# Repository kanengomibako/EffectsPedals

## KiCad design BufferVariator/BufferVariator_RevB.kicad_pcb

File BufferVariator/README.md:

# Buffer Variator
<br>

ギター・ベースのピックアップで拾った音は、楽器本体のボリューム・トーンやシールドケーブル、最初に接続する機器の入力部により独特な音質変化が起こります。本機は、入力部の抵抗値と静電容量値を変化させることにより、主に高音域の音質変化をコントロールできるようにしたバッファー／ブースターです。

### 各部の機能

- INPUT 端子

  パッシブタイプのギターやベースを接続します。フルアップボリュームポットやフルアップトーンポットが搭載されていると、より効果的です。アクティブタイプの楽器や別のバッファーを介して接続した場合、音色変化がほとんどなく、GAINのみ変化します。

- OUTPUT 端子

  アンプや他の機器の入力へ接続します。

- DC9V 端子

  ACアダプターなどの電源を接続します。電源には、DC9V（センターマイナス）出力で、100mA以上の電流出力が可能なものを使用してください。

  ※ 12V以上の電源を接続した場合は、保護回路が働くため動作しません。

- フットスイッチ

  エフェクトオン／オフを切り替えます。エフェクトオフ時は、一般的なバッファー（RESISTANCE：1MΩ　CAPACITANCE：OFF　GAIN：±0dB）となります。

  ※ 一般的なトゥルーバイパスのエフェクターと同程度のスイッチングノイズがあります。

- GAIN

  音量の増減を調整します。

- RESISTANCE

  抵抗値を設定します。抵抗値が上がるほど、高音域が強調された音色になります。代表的な周波数特性変化は下図の通りです。

  <br>※ 10kから反時計回り、10Mから時計回りにはストッパーがあるため回りません。無理な力を加えないようご注意ください。

- CAPACITANCE

  コンデンサの静電容量を設定します。容量値が上がるほど、高音域が減衰した音色になります。ピックアップの種類によりますが、ピークレベルも少し変動します。代表的な周波数特性変化は下図の通りです。

  <br>※ OFFから反時計回り、6800pから時計回りにはストッパーがあるため回りません。無理な力を加えないようご注意ください。

### 使い方の例

- バッファー／ブースター／アッテネーター

  通常のイコライザーでは再現が難しい音色変化があります。音量を上げるだけでなく、下げる目的でも使用することができます。

- シールドケーブルシミュレーション

  シールドケーブルにはコンデンサのように静電容量があります。ケーブルの長さに比例して容量値が大きくなるので、短いケーブルを使用しているときに本機で容量を足すと、長いケーブルを使っているときと同じ音色にすることができます。また、使用したいケーブルの静電容量がわかっている場合、それと同じ容量になるように設定することができます。

- エフェクター入力部の再現

  一部のエフェクターでは、前段にバッファーがあると音色が変化します。そういったエフェクターの前段に使うバッファーとして本機を以下のような設定にしておくと、バッファーなしで接続したときの音をある程度再現することができます。
  
  | 機種             | RESISTANCE | CAPACITANCE |
  | ---------------- | ---------- | ----------- |
  | RAT、Distortion+ | 1M         | 1000p       |
  | Big Muff         | 50k        | OFF         |
  | Fuzz Face        | 10k        | OFF         |
  
  ※ Fuzz Faceは再現度が高くありません。

### 資料
- [Buffer Variator製作に関する記事](https://kanengomibako.github.io/pages/00386_BufferVariator.html)
- [「ボリューム」で考える入出力インピーダンス](https://kanengomibako.github.io/pages/00301.html)
- [ギターケーブルの音への影響](https://zenn.dev/bj_9/articles/ef8c6669f2db6e)（外部サイト）

| 主な仕様 |  |
| - | - |
| 最大入力電圧 | +15.9 dBu（13.7 Vp-p） |
| 最大出力電圧 | +15.7 dBu（13.4 Vp-p） |
| 入力インピーダンス | 1 MΩ（エフェクトオフ時） |
| 出力インピーダンス | 1 kΩ |
| コントロール | エフェクトオン／オフスイッチ　RESISTANCEつまみ　CAPACITANCEつまみ　GAINつまみ |
| インジケーター | 青色LED（エフェクトオン）<br>暗赤色LED（エフェクトオフ） |
| 接続端子 | INPUT端子　OUTPUT端子　電源入力端子 |
| 消費電流 | 16 mA |
| 外形寸法 | 幅 63 mm × 奥行 110 mm × 高さ 51 mm<br/>（つまみ、スイッチ部を除いた高さ 34 mm） |
| 質量 | 306 g（ステンレス筐体バージョン）<br>196 g（アルミニウム筐体バージョン） |

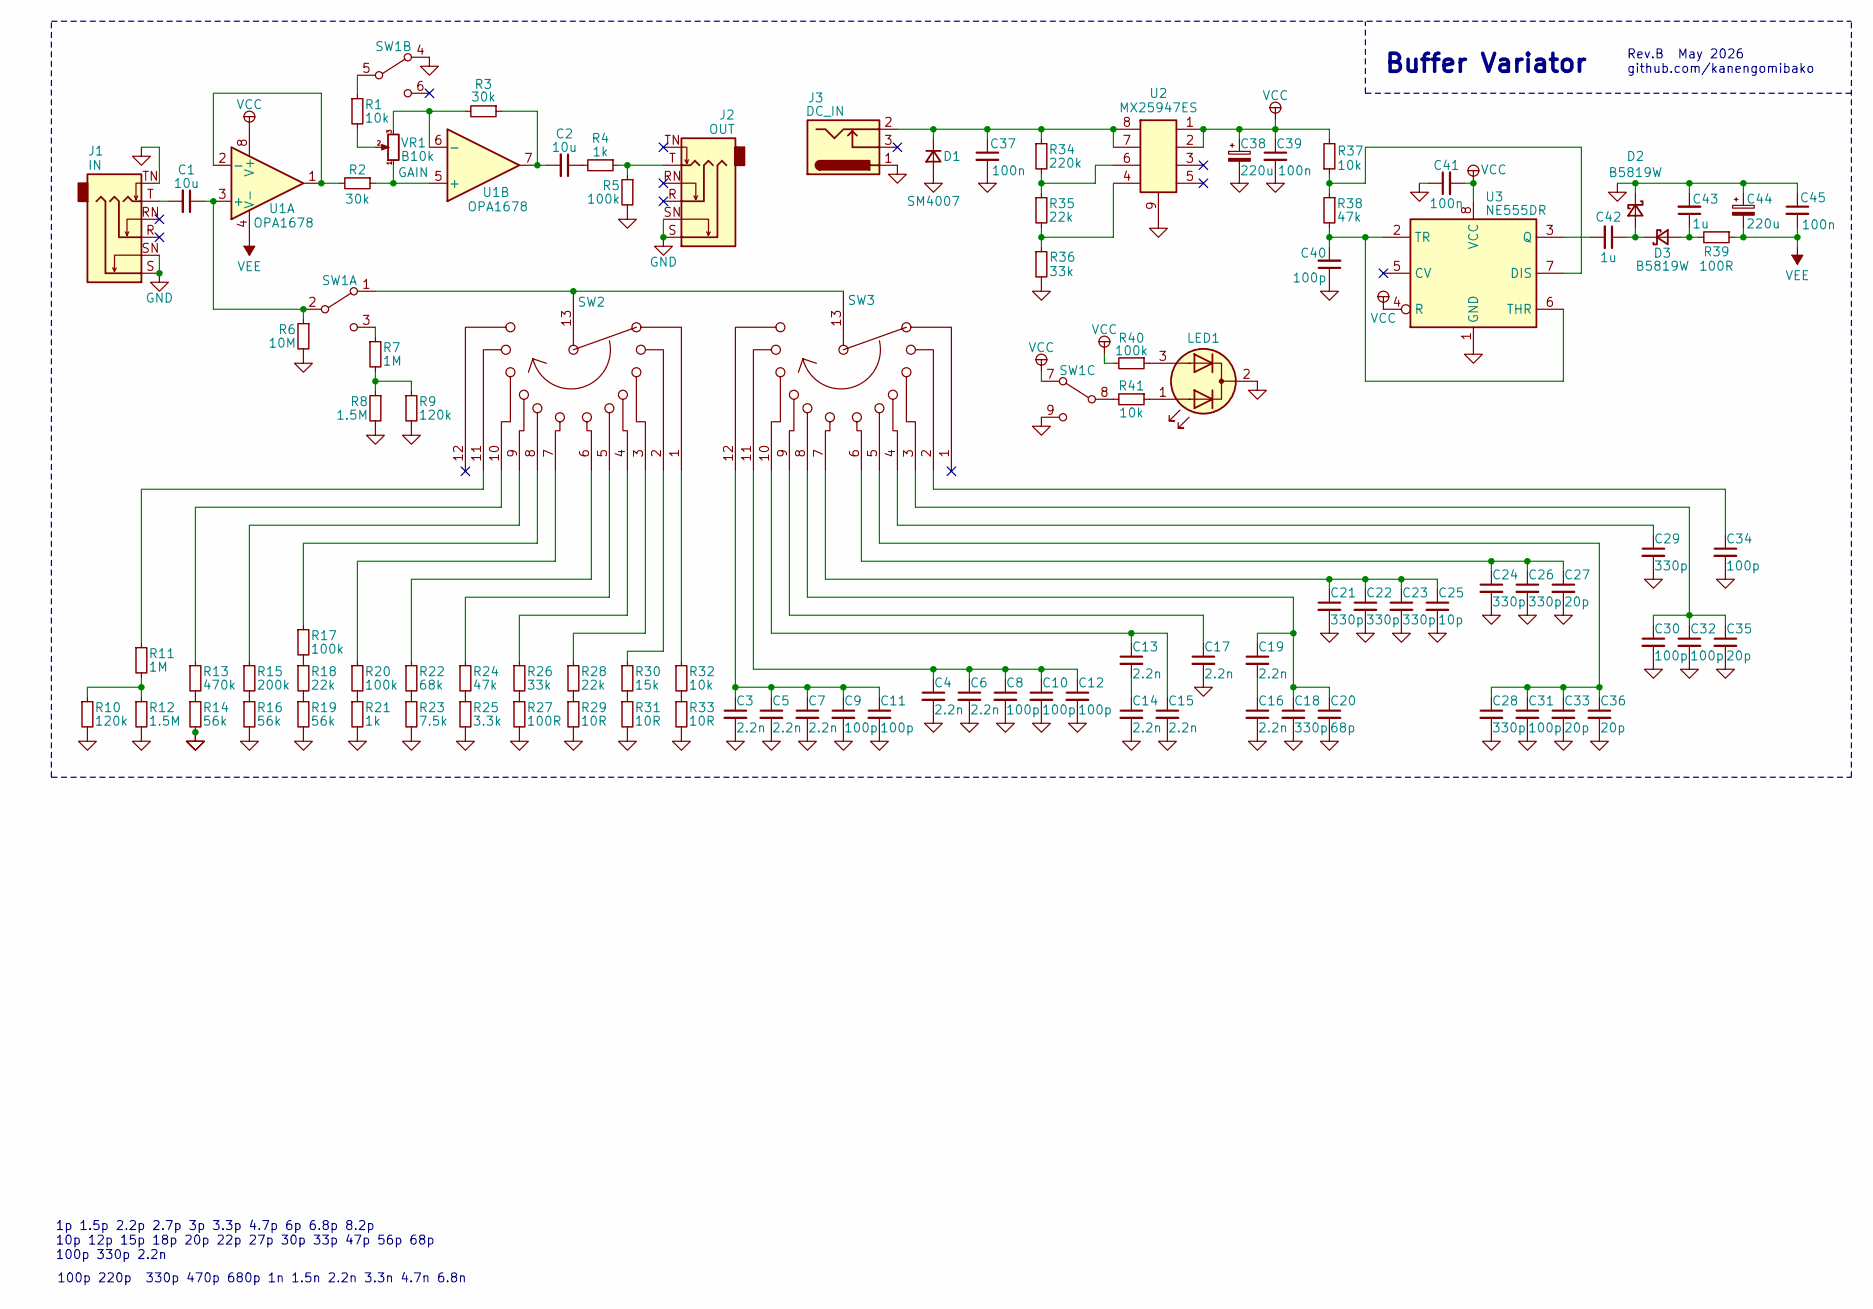
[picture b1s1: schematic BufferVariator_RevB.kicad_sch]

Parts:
C1, C2: 10u; C_1812_4532Metric_THT_P2.0; LCSC C399604
C3, C4, C5, C6, C7, C13, C14, C15, C16, C17, C19: 2.2n; C_0805_2012Metric; LCSC C28260
C8, C9, C10, C11, C12, C30, C31, C32, C34, C40: 100p; C_0603_1608Metric; LCSC C14858
C18, C21, C22, C23, C24, C26, C28, C29: 330p; C_0603_1608Metric; LCSC C1664
C20: 68p; C_0603_1608Metric; LCSC C28262
C25: 10p; C_0603_1608Metric; LCSC C1634
C27, C33, C35, C36: 20p; C_0603_1608Metric; LCSC C1648
C37, C39, C41, C45: 100n; C_0603_1608Metric; LCSC C14663
C38, C44: 220u; my_C_D6.3mm_P2.50mm; LCSC C88729
C42, C43: 1u; C_1206_3216Metric; LCSC C1848
D1: SM4007; D_SOD-123F; LCSC C64898
D2, D3: B5819W; D_SOD-123F; LCSC C8598
J1: IN; PJ-611E_HOOYA; LCSC C309282
J2: OUT; PJ-611E_HOOYA; LCSC C309282
J3: DC_IN; my_DC_Jack; LCSC C319099
LED1: BR_LED; my_LED_3mm_RG; LCSC C2895559
R1, R32, R37, R41: 10k; R_0603_1608Metric; LCSC C25804
R2, R3: 30k; R_0603_1608Metric; LCSC C22984
R4, R21: 1k; R_0603_1608Metric; LCSC C21190
R5, R17, R20, R40: 100k; R_0603_1608Metric; LCSC C25803
R6: 10M; R_0603_1608Metric; LCSC C7250
R7, R11: 1M; R_0603_1608Metric; LCSC C22935
R8, R12: 1.5M; R_0603_1608Metric; LCSC C4172
R9, R10: 120k; R_0603_1608Metric; LCSC C25808
R13: 470k; R_0603_1608Metric; LCSC C23178
R14, R16, R19: 56k; R_0603_1608Metric; LCSC C23206
R15: 200k; R_0603_1608Metric; LCSC C25811
R18, R28, R35: 22k; R_0603_1608Metric; LCSC C31850
R22: 68k; R_0603_1608Metric; LCSC C23231
R23: 7.5k; R_0603_1608Metric; LCSC C23234
R24, R38: 47k; R_0603_1608Metric; LCSC C25819
R25: 3.3k; R_0603_1608Metric; LCSC C22978
R26, R36: 33k; R_0603_1608Metric; LCSC C4216
R27, R39: 100R; R_0603_1608Metric; LCSC C22775
R29, R31, R33: 10R; R_0603_1608Metric; LCSC C22859
R30: 15k; R_0603_1608Metric; LCSC C22809
R34: 220k; R_0603_1608Metric; LCSC C22961
SW1: 3PDT; my_sw_3pdt; LCSC Daier
SW2: Rotary_SW_R; RotarySW_Alpha_26mm_wide_pad; LCSC A-1893 Tayda
SW3: Rotary_SW_C; RotarySW_Alpha_26mm_wide_pad; LCSC A-1893 Tayda
U1: OPA1678; SOIC-8_3.9x4.9mm_P1.27mm_rotate; LCSC C192421
U2: MX25947ES; SOIC-8-1EP_3.9x4.9mm_rotate; LCSC C5875698
U3: NE555DR; SOIC-8_3.9x4.9mm_P1.27mm_rotate; LCSC C7593
VR1: B10k; my_Pot_RD901F-40; LCSC A-7788 Tayda

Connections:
GND: C3.2, C4.2, C5.2, C6.2, C7.2, C8.2, C9.2, C10.2, C11.2, C12.2, C14.2, C15.2, C16.2, C17.2, C18.2, C20.2, C21.2, C22.2, C23.2, C24.2, C25.2, C26.2, C27.2, C28.2, C29.2, C30.2, C31.2, C32.2, C33.2, C34.2, C35.2, C36.2, C37.2, C38.2, C39.2, C40.1, C41.1, C43.2, C44.1, C45.1, D1.2 (A), D2.1 (K), J1.S, J1.SN, J1.TN, J2.S, J2.SN, J3.1, LED1.2 (K), R5.2, R6.2, R8.2, R9.2, R10.2, R12.2, R14.2, R16.2, R19.2, R21.2, R23.2, R25.2, R27.2, R29.2, R31.2, R33.2, R36.2, SW1.4 (A), SW1.9 (C), U2.9 (Pin_8), U3.1 (GND)
unnamed: C1.2, J1.T
unnamed: C2.1, R4.2
unnamed: C2.2, R3.1, U1.7
unnamed: C4.1, C6.1, C8.1, C10.1, C12.1, SW3.11
unnamed: C3.1, C5.1, C7.1, C9.1, C11.1, SW3.12
unnamed: C13.1, C15.1, SW3.10
unnamed: C13.2, C14.1
unnamed: C16.1, C19.2
unnamed: C17.1, SW3.9
unnamed: C18.1, C19.1, C20.1, SW3.8
unnamed: C21.1, C22.1, C23.1, C25.1, SW3.7
unnamed: C24.1, C26.1, C27.1, SW3.6
unnamed: C28.1, C31.1, C33.1, C36.1, SW3.5
unnamed: C29.1, SW3.4
unnamed: C30.1, C32.1, C35.1, SW3.3
unnamed: C34.1, SW3.2
unnamed: C37.1, D1.1 (K), J3.2, R34.1, U2.7, U2.8
unnamed: C42.1, D2.2 (A), D3.1 (K)
unnamed: C43.1, D3.2 (A), R39.2
unnamed: J2.T, R4.1, R5.1
unnamed: LED1.1 (A1), R41.1
unnamed: LED1.3 (A2), R40.1
unnamed: R1.2, VR1.2
unnamed: R7.2, R8.1, R9.1
unnamed: R10.1, R11.2, R12.1
unnamed: R11.1, SW2.11
unnamed: R13.1, SW2.10
unnamed: R13.2, R14.1
unnamed: R15.1, SW2.9
unnamed: R15.2, R16.1
unnamed: R17.1, SW2.8
unnamed: R17.2, R18.1
unnamed: R18.2, R19.1
unnamed: R20.1, SW2.7
unnamed: R20.2, R21.1
unnamed: R22.1, SW2.6
unnamed: R22.2, R23.1
unnamed: R24.1, SW2.5
unnamed: R24.2, R25.1
unnamed: R26.1, SW2.4
unnamed: R26.2, R27.1
unnamed: R28.1, SW2.3
unnamed: R28.2, R29.1
unnamed: R30.1, SW2.2
unnamed: R30.2, R31.1
unnamed: R32.1, SW2.1
unnamed: R32.2, R33.1
unnamed: SW1.1 (A), SW2.13, SW3.13
unnamed: C1.1, R6.1, SW1.2 (B), U1.3 (+)
unnamed: R7.1, SW1.3 (C)
unnamed: R1.1, SW1.5 (B)
unnamed: R41.2, SW1.8 (B)
unnamed: R2.2, U1.1, U1.2 (-)
unnamed: R2.1, U1.5 (+), VR1.1
unnamed: R3.2, U1.6 (-), VR1.3
unnamed: R35.2, R36.1, U2.4
unnamed: R34.2, R35.1, U2.6
unnamed: R37.1, R38.1, U3.7 (DIS)
unnamed: C42.2, U3.3 (Q)
unnamed: C40.2, R38.2, U3.2 (TR), U3.6 (THR)
VCC: C38.1, C39.1, C41.2, R37.2, R40.2, SW1.7 (A), U1.8 (V+), U2.1, U2.2, U3.4 (R), U3.8 (VCC)
VEE: C44.2, C45.2, R39.1, U1.4 (V-)

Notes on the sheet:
100p 220p 330p 470p 680p 1n 1.5n 2.2n 3.3n 4.7n 6.8n
Buffer Variator
1p 1.5p 2.2p 2.7p 3p 3.3p 4.7p 6p 6.8p 8.2p 10p 12p 15p 18p 20p 22p 27p 30p 33p 47p 56p 68p 100p 330p 2.2n
Rev.B May 2026 github.com/kanengomibako

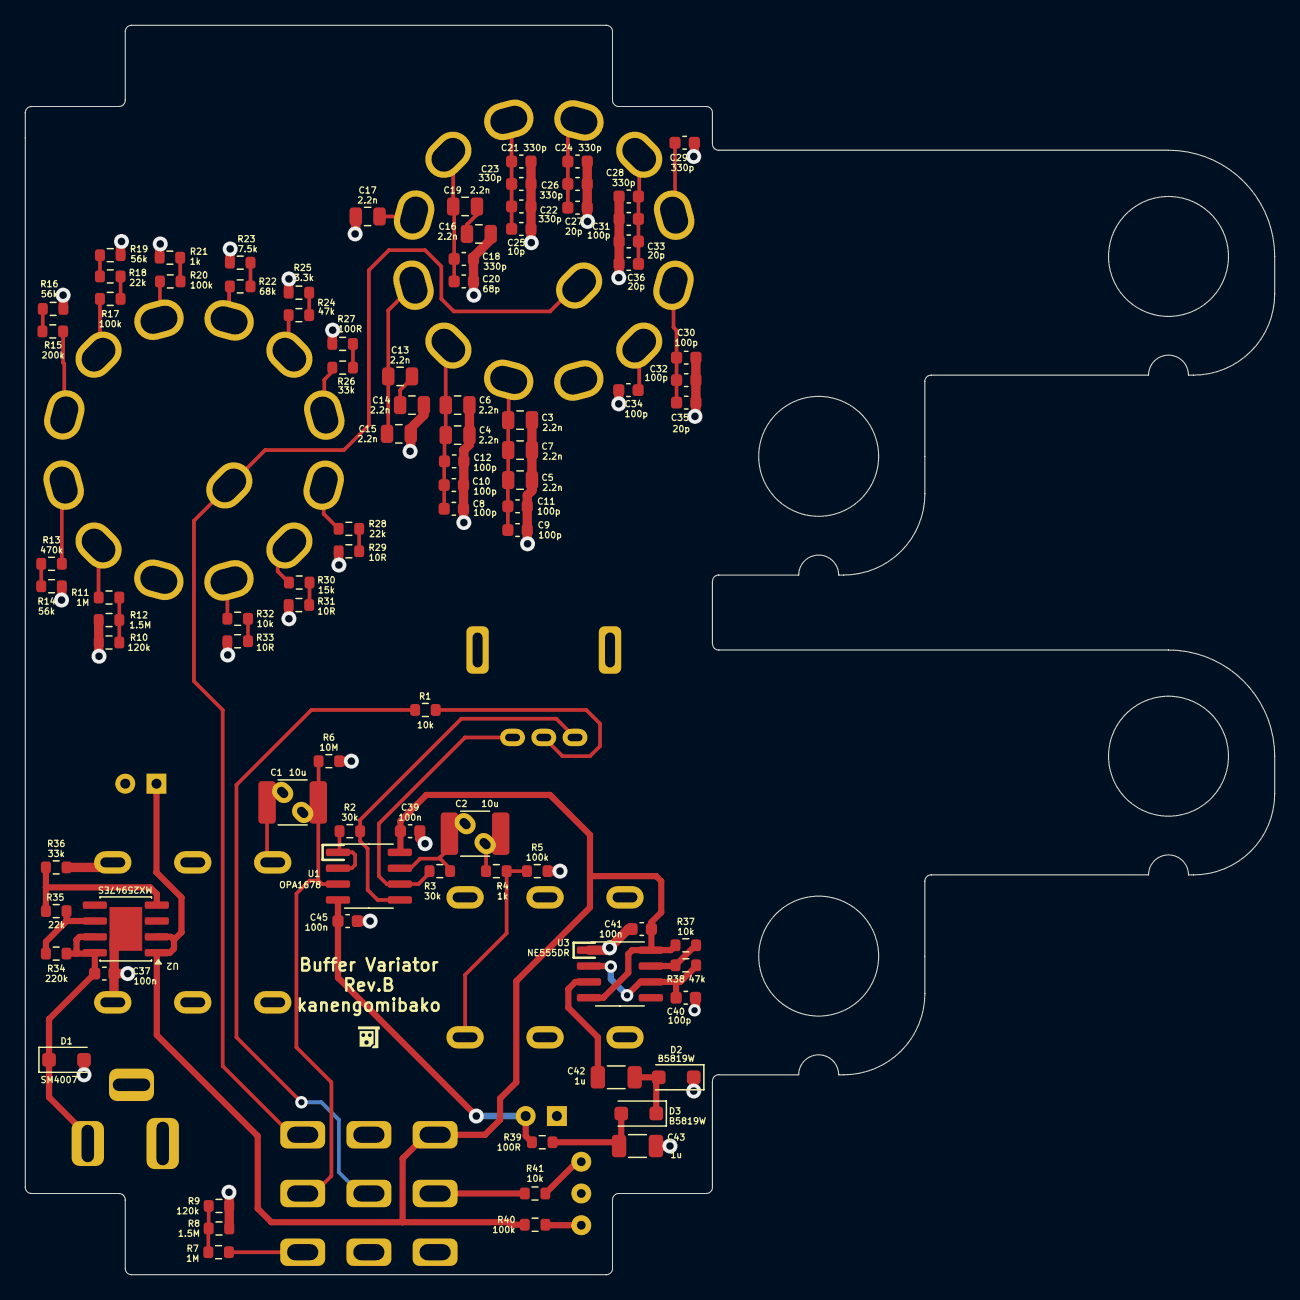
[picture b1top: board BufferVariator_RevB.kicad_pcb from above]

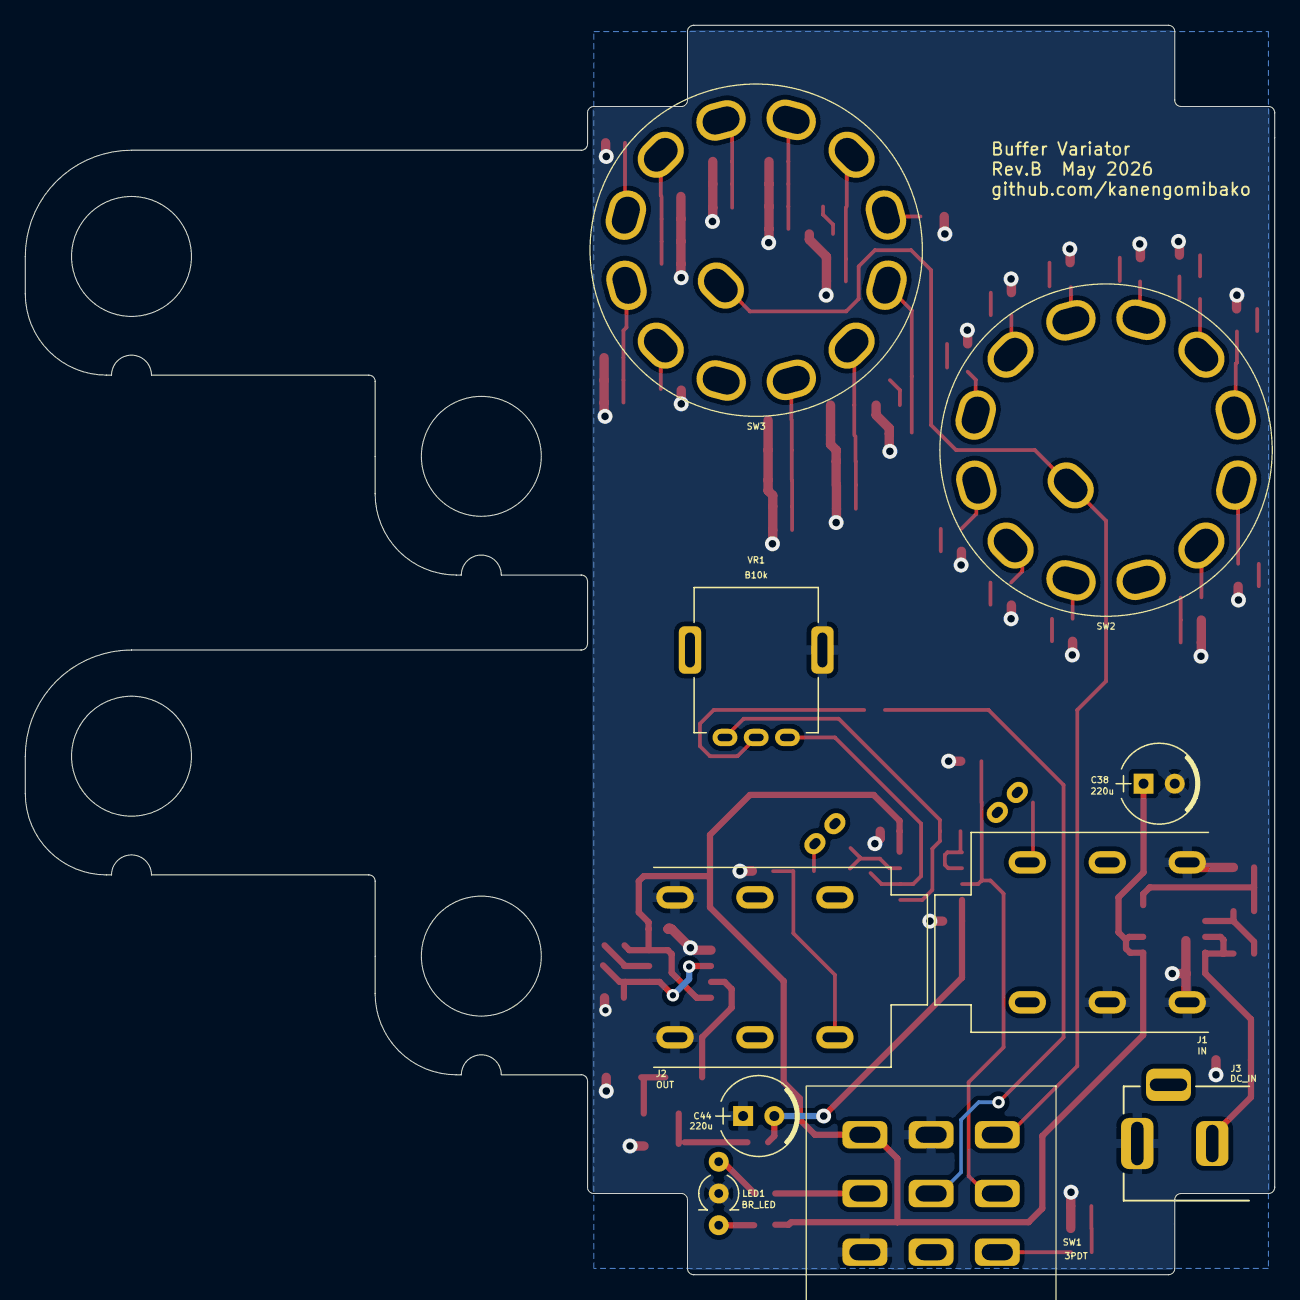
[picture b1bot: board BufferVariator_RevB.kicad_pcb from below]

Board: 2 copper layers, 100.0 x 100.0 mm, 100 parts (10 on the bottom side), 63 nets.

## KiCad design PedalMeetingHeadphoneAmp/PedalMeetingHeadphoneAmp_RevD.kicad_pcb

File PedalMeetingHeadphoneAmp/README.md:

# Pedal Meeting Headphone Amp
<br>

エフェクター展示会の試奏ブースでのコミュニケーションを円滑にするために設計されたヘッドフォンアンプです。ギター／ベースの音と会話用のマイク音声をミックスし、ヘッドフォンで聴くことができます。試奏者と出展者が音を共有できると共に、ヘッドフォンを外さずに会話することが可能となります。

※ 電源は、DC9V（センターマイナス）出力のACアダプターで、0.3A以上の電流出力が可能なものを使用してください。

### ■ 入力

それぞれ独立したゲイン調整を備えています。ゲインを上げ過ぎるとハウリングが起こることがありますのでご注意ください。

- INST

  楽器側の音声出力を接続します。アンプ・キャビネットシミュレータからの接続を想定しています。ゲインは基本的に中央で固定し、微調整として使用してください。

- MIC1／MIC2

  外部マイクを接続します。48Vファンタム電源が必要なマイクには対応していません。

- MIC3

  本体トップ面にあるマイクです。外部マイクがない場合でも、会話を拾うことが可能です。

### ■ 出力

楽器の音とマイクの音をそれぞれ出力ボリュームで調整できます。

- PHONES A／B

  試奏者用、出展者用のヘッドフォンを接続します。

- LINE A／B

  外部録音機器を接続できます。

### ■ スイッチ

- MIC ON／OFF

  すべてのマイク入力を一括でミュートします。マイクが楽器の生音を拾うため、会話時以外はマイクをOFF（LED消灯）にすることをお勧めします。

- MIC 5V

  プラグインパワー方式のコンデンサーマイク（[BEHRINGER BC LAV](https://www.electori-br.jp/products/1043.html) 等）を使用する際にONにします。ダイナミックマイク接続時はOFFにします。48Vファンタム電源が必要なマイクには対応していません。

### ■ 資料
- [Pedal Meeting Headphone Amp製作に関する記事](https://kanengomibako.github.io/pages/00384_PedalMeetingHeadphoneAmp.html)

- ブロック図

  <br>

| ■ 主な仕様 |  |
| - | - |
| 入力インピーダンス | 47kΩ（INST）<br>10kΩ（MIC） |
| 出力インピーダンス | 1 kΩ（LINE）<br>10Ω（PHONES） |
| 最大出力レベル | 2.5 Vrms（LINE）<br>50 mW + 50 mW, 32Ω（PHONES） |
| コントロール | MIC ON／OFFスイッチ　MIC 5Vスイッチ　GAINつまみ × 4　VOLつまみ × 4 |
| インジケーター | 赤色LED（電源ON）<br>青色LED（マイクON） |
| 接続端子 | INST　MIC1／2　PHONES A／B　LINE A／B　電源入力端子 |
| 消費電流 | 40 mA（無信号時）<br>300 mA（最大出力時） |
| 外形寸法 | 幅 100 mm × 奥行 130 mm × 高さ 57 mm |
| 質量 | 550 g |

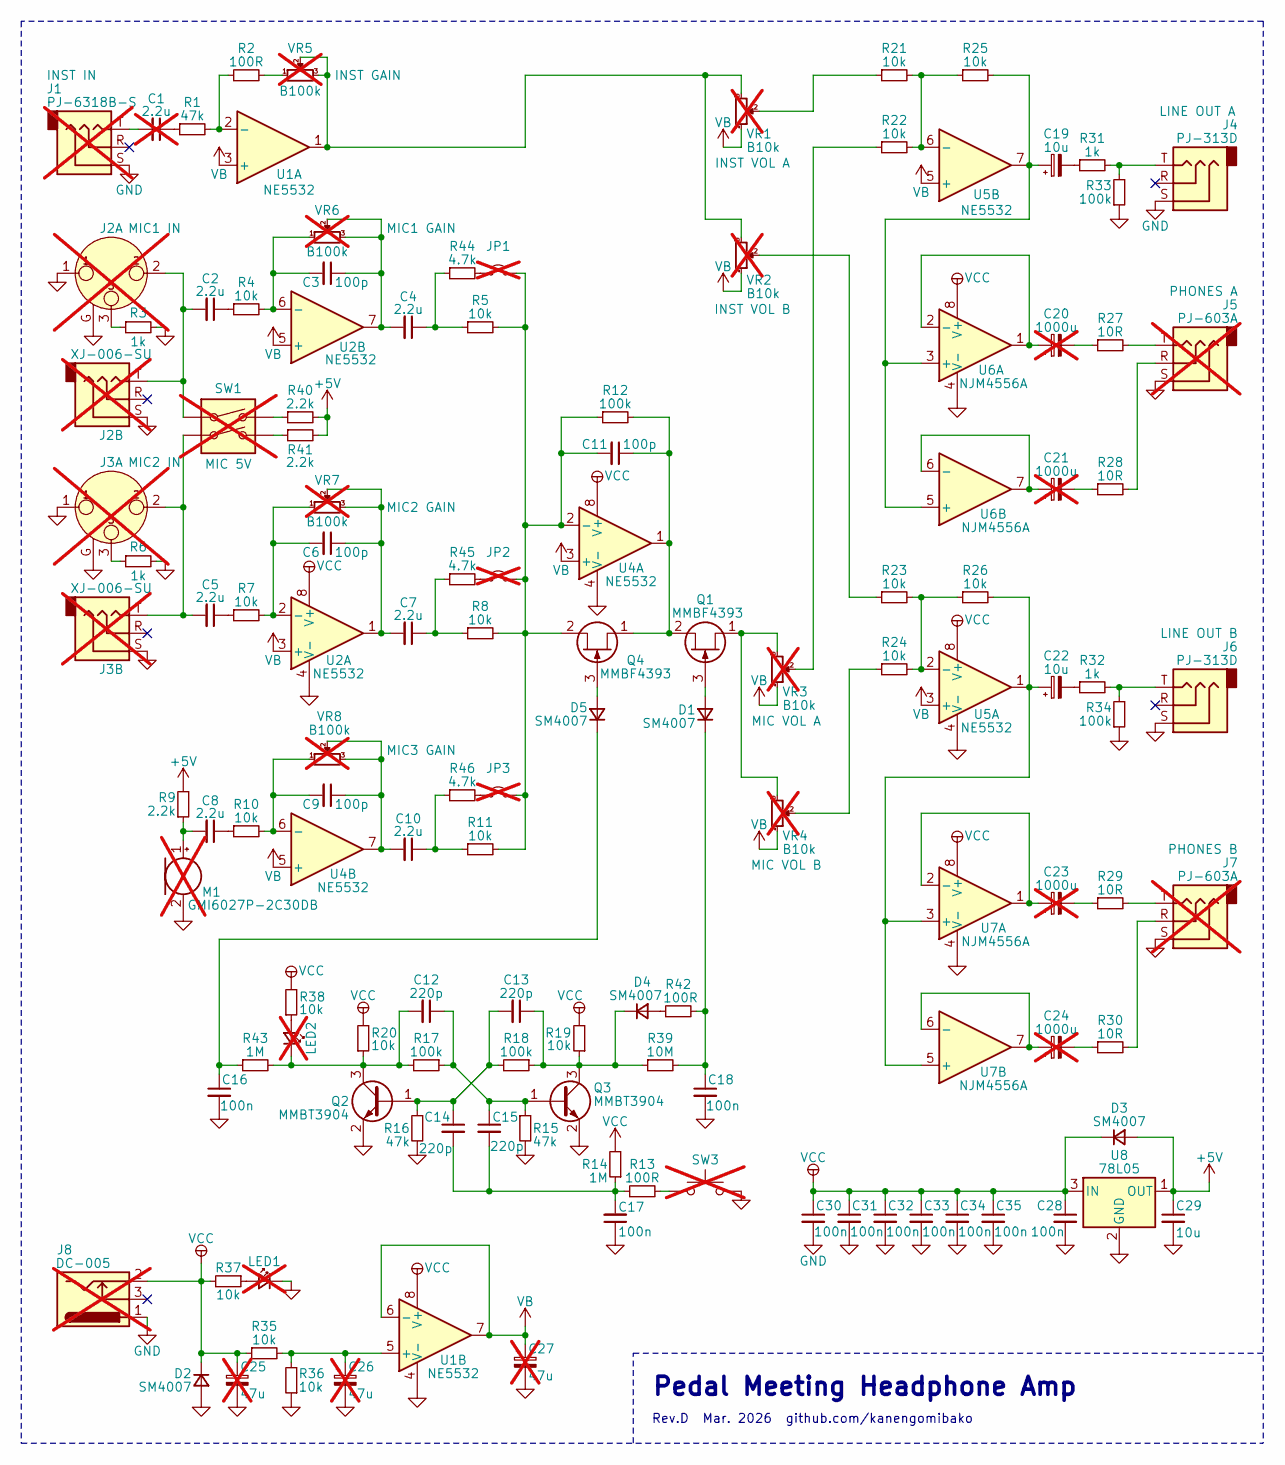
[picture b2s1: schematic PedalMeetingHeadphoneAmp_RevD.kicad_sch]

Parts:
C1: 2.2u; CP_3216-THD; LCSC C178482; not fitted
C2, C4, C5, C7, C8, C10: 2.2u; C_0805_2012Metric; LCSC C377773
C3, C6, C9, C11: 100p; C_0603_1608Metric; LCSC C14858
C12, C13, C14, C15: 220p; C_0603_1608Metric; LCSC C1603
C16, C17, C18, C28, C30, C31, C32, C33, C34, C35: 100n; C_0603_1608Metric; LCSC C14663
C19, C22: 10u; CP_3216-THD; LCSC C7171
C20, C21, C23, C24: 1000u; CP_Radial_D10.0mm_P5.00mm; LCSC C338175; not fitted
C25, C26, C27: 47u; CP_Radial_D5.0mm_P2.00mm; LCSC C216203; not fitted
C29: 10u; C_0805_2012Metric; LCSC C15850
D1, D2, D3, D4, D5: SM4007; D_SOD-123F; LCSC C64898
J1: PJ-6318B-S; PJ-6318; LCSC C50176625; not fitted
J2, J3: XJ-006-SU; Jack_XLR-6.35mm_Neutrik_NCJ6FA-H-0_Horizontal; LCSC C309332; not fitted
J4, J6: PJ-313D; PJ-313D_HOOYA; LCSC C2939579
J5, J7: PJ-603A; LCSC C309273; not fitted
J8: DC-005; my_DC_Jack; LCSC C319099; not fitted
JP1, JP2, JP3: JP; my_SolderJumper-THpad; not fitted
LED1: Red_LED; my_LED_3mm; LCSC C440523; not fitted
LED2: Blue_LED; my_LED_3mm; LCSC C330760; not fitted
M1: GMI6027P-2C30DB; my_conn; LCSC C233898; not fitted
Q1, Q4: MMBF4393; SOT-23_rotate; LCSC C152291
Q2, Q3: MMBT3904; SOT-23_rotate; LCSC C20526
R1, R15, R16: 47k; R_0603_1608Metric; LCSC C25819
R2, R13, R42: 100R; R_0603_1608Metric; LCSC C22775
R3, R6, R31, R32: 1k; R_0603_1608Metric; LCSC C21190
R4, R5, R7, R8, R10, R11, R19, R20, R21, R22, R23, R24, R25, R26, R35, R36, R37, R38: 10k; R_0603_1608Metric; LCSC C25804
R9, R40, R41: 2.2k; R_0603_1608Metric; LCSC C4190
R12: 100k; my_R_0603_smd_thd_P7mm; LCSC C25803
R14, R43: 1M; R_0603_1608Metric; LCSC C22935
R17, R18, R33, R34: 100k; R_0603_1608Metric; LCSC C25803
R27, R28, R29, R30: 10R; R_1206_3216Metric; LCSC C17903
R39: 10M; R_0603_1608Metric; LCSC C7250
R44, R45, R46: 4.7k; R_0603_1608Metric; LCSC C23162
SW1: SW_DIP; SW_DIP_SPSTx02_Slide_9.78x7.26mm_W7.62mm_P2.54mm; LCSC C3040968; not fitted
SW3: SW; SW_Cherry_MX_1.00u_PCB; LCSC C412378; not fitted
U1, U2, U4, U5: NE5532; SOIC-8_3.9x4.9mm_P1.27mm_rotate; LCSC C7426
U6, U7: NJM4556A; my_DMP8; LCSC C3018893
U8: 78L05; SOT-89-3_rotate180; LCSC C71136
VR1, VR2, VR3, VR4: B10k; my_pot123_hole; LCSC A-5654 tayda; not fitted
VR5, VR6, VR7, VR8: B100k; my_Pot_PTV09_deep; LCSC A-5530 tayda; not fitted

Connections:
+5V: C29.1, D3.2 (A), R9.2, R40.2, R41.2, U8.1 (OUT)
GND: C16.2, C17.1, C18.2, C25.2, C26.2, C27.2, C28.2, C29.2, C30.2, C31.2, C32.2, C33.2, C34.2, C35.2, D2.2 (A), J1.S, J2.1, J2.G, J2.S, J3.1, J3.G, J3.S, J4.S, J5.S, J6.S, J7.S, J8.1, LED1.1 (K), M1.2 (-), Q2.2 (E), Q3.2 (E), R3.2, R6.2, R15.2, R16.2, R33.1, R34.1, R36.1, SW3.2, U1.4 (V-), U2.4 (V-), U4.4 (V-), U5.4 (V-), U6.4 (V-), U7.4 (V-), U8.2 (GND)
unnamed: C1.1, R1.1
unnamed: C1.2, J1.T
unnamed: C2.1, R4.1
unnamed: C2.2, J2.2, J2.T, SW1.1
unnamed: C3.1, C4.2, U2.7, VR6.2, VR6.3
unnamed: C4.1, R5.1, R44.1
unnamed: C5.1, R7.1
unnamed: C5.2, J3.2, J3.T, SW1.2
unnamed: C6.1, C7.2, U2.1, VR7.2, VR7.3
unnamed: C7.1, R8.1, R45.1
unnamed: C8.1, R10.1
unnamed: C10.1, R11.1, R46.1
unnamed: C9.1, C10.2, U4.7, VR8.2, VR8.3
unnamed: C14.2, C15.2, C17.2, R13.1, R14.1
unnamed: C19.2, R31.1
unnamed: C20.2, R27.1
unnamed: C21.2, R28.1
unnamed: C22.2, R32.1
unnamed: C23.2, R29.1
unnamed: C24.2, R30.1
unnamed: D1.2 (A), Q1.3 (G)
unnamed: C18.1, D1.1 (K), R39.2, R42.2
unnamed: D4.2 (A), R42.1
unnamed: C13.1, D4.1 (K), Q3.3 (C), R18.1, R19.1, R39.1
unnamed: D5.2 (A), Q4.3 (G)
unnamed: C16.1, D5.1 (K), R43.1
unnamed: J2.3, R3.1
unnamed: J3.3, R6.1
unnamed: J4.T, R31.2, R33.2
unnamed: J5.R, R28.2
unnamed: J5.T, R27.2
unnamed: J6.T, R32.2, R34.2
unnamed: J7.R, R30.2
unnamed: J7.T, R29.2
unnamed: JP1.1 (A), R44.2
unnamed: C11.2, JP1.2 (B), JP2.2 (B), JP3.2 (B), Q4.2 (S), R5.2, R8.2, R11.2, R12.1, U4.2 (-)
unnamed: JP2.1 (A), R45.2
unnamed: JP3.1 (A), R46.2
unnamed: LED1.2 (A), R37.1
unnamed: LED2.2 (A), R38.1
unnamed: C12.2, LED2.1 (K), Q2.3 (C), R17.2, R20.1, R43.2
unnamed: C8.2, M1.1 (+), R9.1
unnamed: Q1.1 (D), VR3.3, VR4.3
unnamed: C11.1, Q1.2 (S), Q4.1 (D), R12.2, U4.1
unnamed: C13.2, C14.1, Q2.1 (B), R16.1, R18.2
unnamed: C12.1, C15.1, Q3.1 (B), R15.1, R17.1
unnamed: R2.2, VR5.1
unnamed: R13.2, SW3.1
unnamed: R21.1, VR1.2
unnamed: R22.1, VR3.2
unnamed: R23.1, VR2.2
unnamed: R24.1, VR4.2
unnamed: R40.1, SW1.4
unnamed: R41.1, SW1.3
unnamed: U1.1, VR1.3, VR2.3, VR5.2, VR5.3
unnamed: R1.2, R2.1, U1.2 (-)
unnamed: C26.1, R35.2, R36.2, U1.5 (+)
unnamed: C6.2, R7.2, U2.2 (-), VR7.1
unnamed: C3.2, R4.2, U2.6 (-), VR6.1
unnamed: C9.2, R10.2, U4.6 (-), VR8.1
unnamed: R23.2, R24.2, R26.1, U5.2 (-)
unnamed: R21.2, R22.2, R25.1, U5.6 (-)
unnamed: C19.1, R25.2, U5.7, U6.3 (+), U6.5 (+)
unnamed: C20.1, U6.1, U6.2 (-)
unnamed: C21.1, U6.6 (-), U6.7
unnamed: C22.1, R26.2, U5.1, U7.3 (+), U7.5 (+)
unnamed: C23.1, U7.1, U7.2 (-)
unnamed: C24.1, U7.6 (-), U7.7
VB: C27.1, U1.3 (+), U1.6 (-), U1.7, U2.3 (+), U2.5 (+), U4.3 (+), U4.5 (+), U5.3 (+), U5.5 (+), VR1.1, VR2.1, VR3.1, VR4.1
VCC: C25.1, C28.1, C30.1, C31.1, C32.1, C33.1, C34.1, C35.1, D2.1 (K), D3.1 (K), J8.2, R14.2, R19.2, R20.2, R35.1, R37.2, R38.2, U1.8 (V+), U2.8 (V+), U4.8 (V+), U5.8 (V+), U6.8 (V+), U7.8 (V+), U8.3 (IN)

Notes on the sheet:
Pedal Meeting Headphone Amp
Rev.D Mar. 2026 github.com/kanengomibako

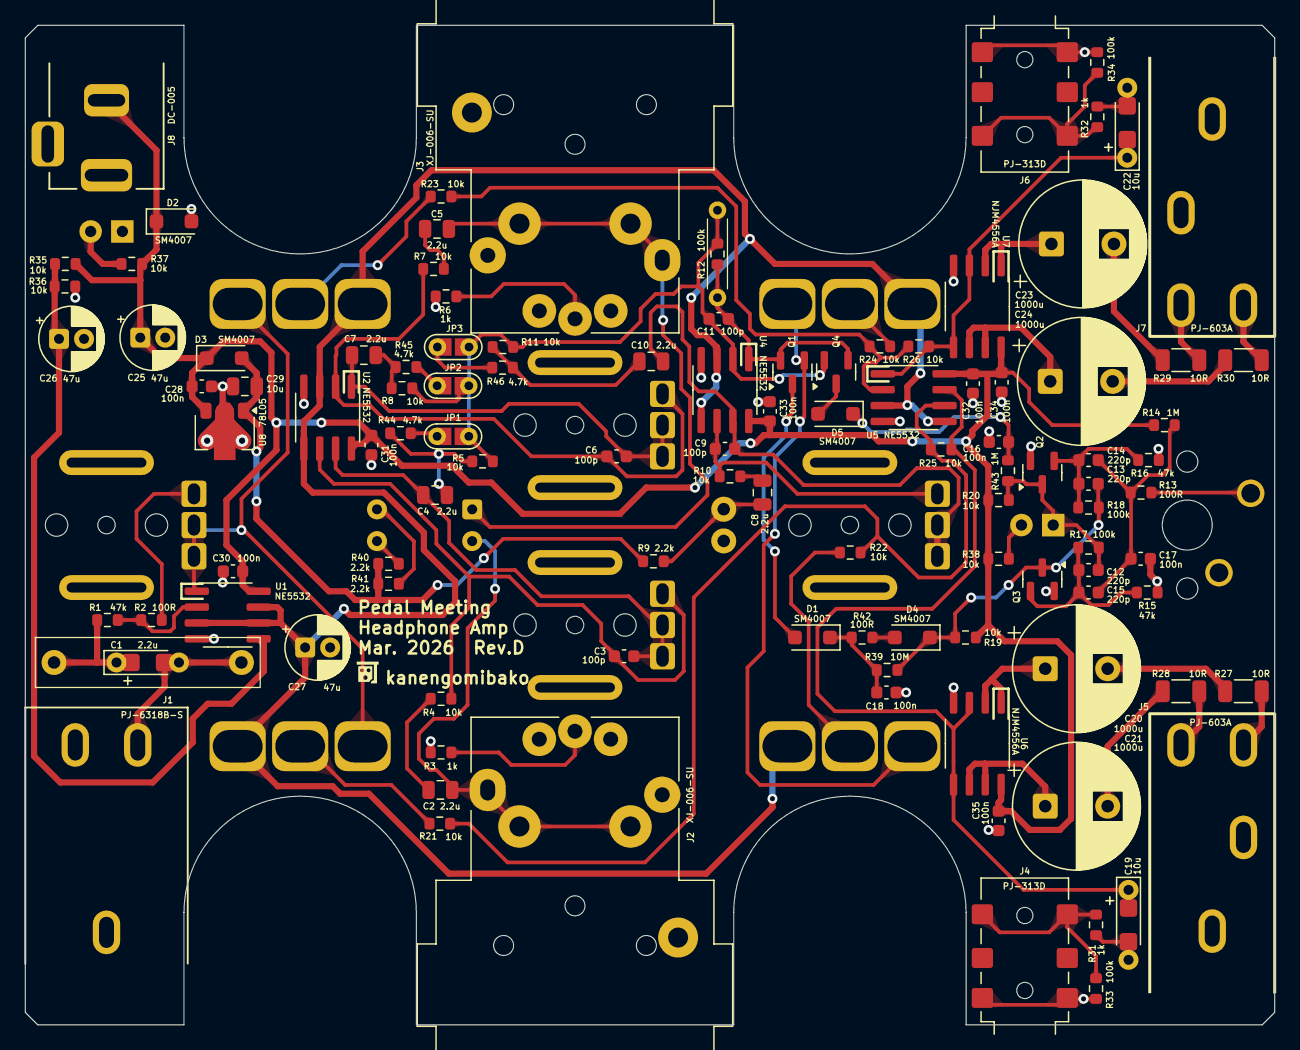
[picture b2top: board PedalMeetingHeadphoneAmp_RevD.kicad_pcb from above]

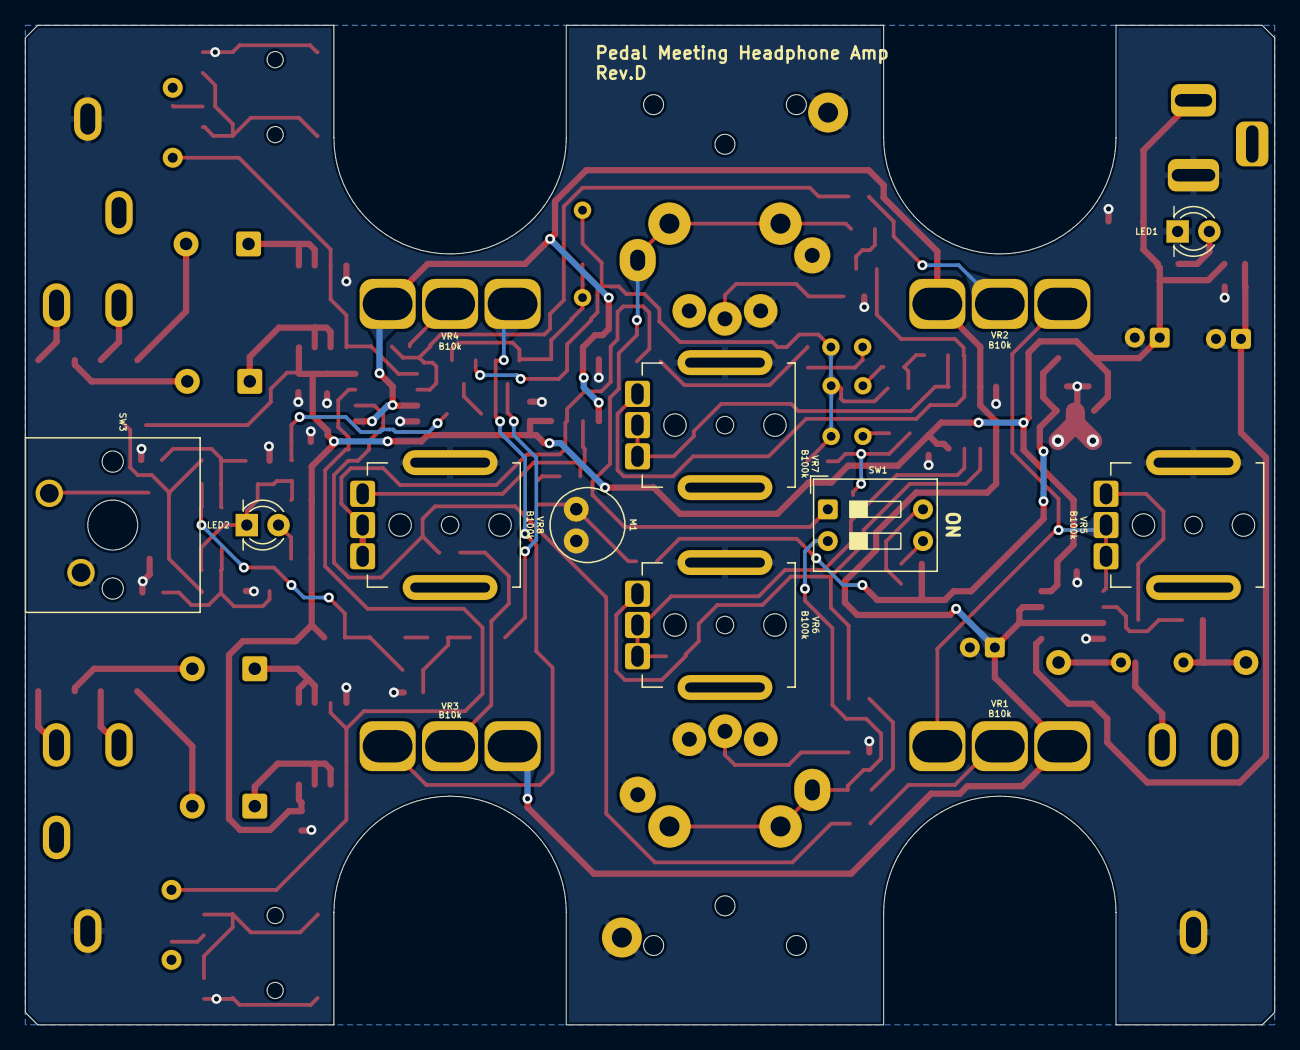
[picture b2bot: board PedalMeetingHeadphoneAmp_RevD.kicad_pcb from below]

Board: 2 copper layers, 100.0 x 80.0 mm, 121 parts (13 on the bottom side), 72 nets.

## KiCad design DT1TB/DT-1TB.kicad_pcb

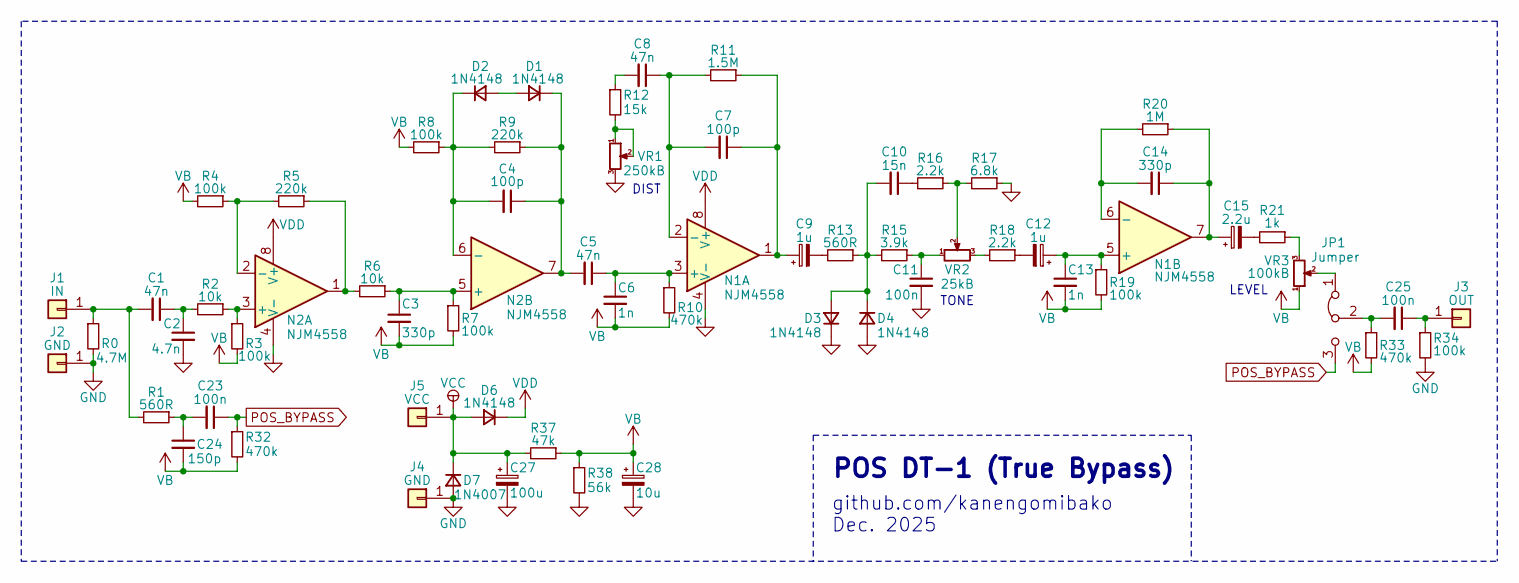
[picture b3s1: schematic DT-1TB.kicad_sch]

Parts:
C1, C5, C8: 47n; my_C_Rect1_P5.00mm
C2: 4.7n; my_C_Rect1_P5.00mm
C3, C14: 330p; my_C_Disc_P2.50mm
C4, C7: 100p; my_C_Disc_P2.50mm
C6, C13: 1n; my_C_Rect1_P5.00mm
C9, C12: 1u; my_C_D5.0mm_P2.50mm
C10: 15n; my_C_Rect1_P5.00mm
C11, C23, C25: 100n; my_C_Rect1_P5.00mm
C15: 2.2u; my_C_D5.0mm_P2.50mm
C24: 150p; my_C_Disc_P2.50mm
C27: 100u; my_C_D5.0mm_P2.50mm
C28: 10u; my_C_D5.0mm_P2.50mm
D1, D2, D6: 1N4148; my_D_P5.08mm_Horizontal
D3, D4: 1N4148; my_D_P7.62mm
D7: 1N4007; my_D_P7.62mm
J1: IN; my_WirePad_1mmDrill
J2, J4: GND; my_WirePad_1mmDrill
J3: OUT; my_WirePad_1mmDrill
J5: VCC; my_WirePad_1mmDrill
JP1: Jumper; PinHeader_1x03_P2.54mm_Vertical
N1, N2: NJM4558; DIP-8_W7.62mm_Socket
R0: 4.7M; my_R_P7.62mm_Horizontal
R1, R13: 560R; my_R_P7.62mm_Horizontal
R2, R6: 10k; my_R_P7.62mm_Horizontal
R3, R4, R7, R8, R19, R34: 100k; my_R_P7.62mm_Horizontal
R5, R9: 220k; my_R_P7.62mm_Horizontal
R10, R32, R33: 470k; my_R_P7.62mm_Horizontal
R11: 1.5M; my_R_P7.62mm_Horizontal
R12: 15k; my_R_P7.62mm_Horizontal
R15: 3.9k; my_R_P7.62mm_Horizontal
R16, R18: 2.2k; my_R_P7.62mm_Horizontal
R17: 6.8k; my_R_P7.62mm_Horizontal
R20: 1M; my_R_P7.62mm_Horizontal
R21: 1k; my_R_P7.62mm_Horizontal
R37: 47k; my_R_P7.62mm_Horizontal
R38: 56k; my_R_P7.62mm_Horizontal
VR1: 250kB; my_pot_5mm
VR2: 25kB; my_pot_5mm
VR3: 100kB; my_pot_5mm

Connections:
GND: C2.2, C11.2, C27.2, C28.2, D3.1 (K), D4.2 (A), D7.2 (A), J2.1, J4.1, N1.4 (V-), N2.4 (V-), R0.2, R17.1, R34.2, R38.2, VR1.3
unnamed: C1.1, C2.1, R2.2
unnamed: C7.1, C9.1, N1.1, R11.1
unnamed: C8.2, R12.1
unnamed: C9.2, R13.2
unnamed: C10.1, R16.2
unnamed: C11.1, R15.1, VR2.1
unnamed: C12.2, R18.1
unnamed: C14.1, C15.1, N1.7, R20.1
unnamed: C15.2, R21.2
unnamed: C23.2, C24.1, R1.1
unnamed: D1.2 (A), D2.2 (A)
unnamed: C4.1, C5.2, D1.1 (K), N2.7, R9.1
unnamed: C4.2, D2.1 (K), N2.6 (-), R8.1, R9.2
unnamed: C10.2, D3.2 (A), D4.1 (K), R13.1, R15.2
unnamed: C1.2, J1.1, R0.1, R1.2
unnamed: C25.1, J3.1, R34.1
unnamed: JP1.1 (A), VR3.2
unnamed: C25.2, JP1.2 (C), R33.1
unnamed: C5.1, C6.1, N1.3 (+), R10.1
unnamed: C7.2, C8.1, N1.2 (-), R11.2
unnamed: C12.1, C13.1, N1.5 (+), R19.1
unnamed: C14.2, N1.6 (-), R20.2
unnamed: N2.1, R5.1, R6.2
unnamed: N2.3 (+), R2.1, R3.1
unnamed: N2.2 (-), R4.1, R5.2
unnamed: C3.1, N2.5 (+), R6.1, R7.1
unnamed: R12.2, VR1.1, VR1.2
unnamed: R16.1, R17.2, VR2.2
unnamed: R18.2, VR2.3
unnamed: R21.1, VR3.3
POS_BYPASS: C23.1, JP1.3 (B), R32.1
VB: C3.2, C6.2, C13.2, C24.2, C28.1, R3.2, R4.2, R7.2, R8.2, R10.2, R19.2, R32.2, R33.2, R37.1, R38.1, VR3.1
VCC: C27.1, D6.2 (A), D7.1 (K), J5.1, R37.2
VDD: D6.1 (K), N1.8 (V+), N2.8 (V+)

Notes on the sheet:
TONE
LEVEL
github.com/kanengomibako Dec. 2025
DIST
POS DT-1 (True Bypass)

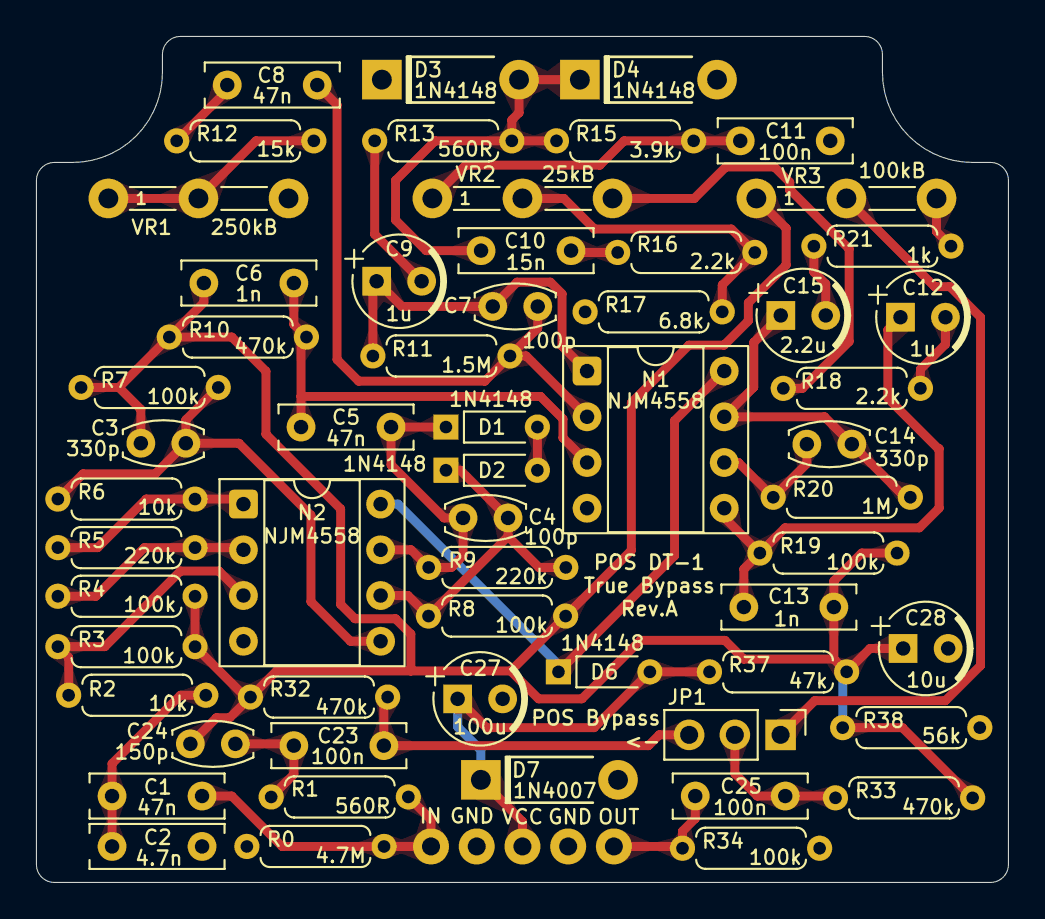
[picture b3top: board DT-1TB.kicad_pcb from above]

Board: 2 copper layers, 54.0 x 47.0 mm, 63 parts (0 on the bottom side), 35 nets.
